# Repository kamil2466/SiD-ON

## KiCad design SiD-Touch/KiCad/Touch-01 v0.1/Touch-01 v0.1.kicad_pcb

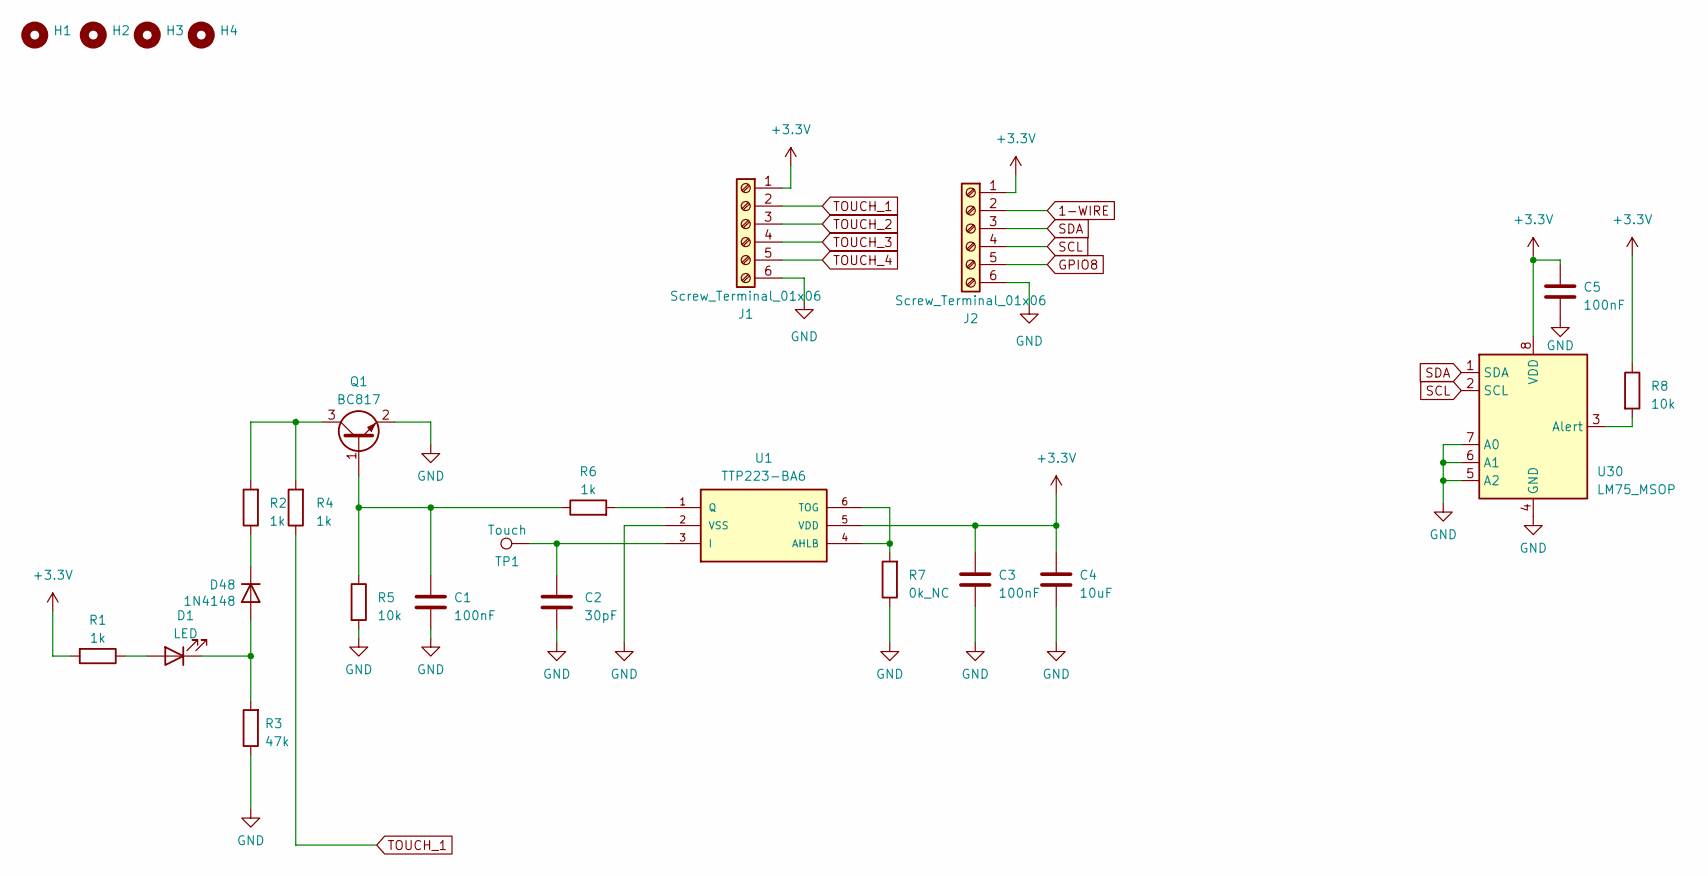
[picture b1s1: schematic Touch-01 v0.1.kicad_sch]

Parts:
C1, C3, C5: 100nF; C_0603_1608Metric
C2: 30pF; C_0603_1608Metric
C4: 10uF; C_0603_1608Metric
D1: LED; LED_1206_3216Metric
D48: 1N4148; D_MiniMELF; JLCPCB C68883
H1, H2, H3, H4: MountingHole; MountingHole_3.2mm_M3_ISO7380_Pad
J1, J2: Screw_Terminal_01x06; PinSocket_1x06_P2.54mm_Vertical
Q1: BC817; SOT-23
R1, R2, R4, R6: 1k; R_0603_1608Metric
R3: 47k; R_0603_1608Metric
R5, R8: 10k; R_0603_1608Metric
R7: 0k_NC; R_0603_1608Metric
TP1: Touch; TestPoint_Pad_D4.0mm
U1: TTP223-BA6; SOT-23-6; MANUFACTURER_PART_NUMBER TTP223-BA6
U30: LM75_MSOP; MSOP-8_3x3mm_P0.65mm

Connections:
1-WIRE: J2.2
+3V3: C3.1, C4.1, C5.1, J1.1, J2.1, R1.2, R8.1, U1.5 (VDD); also elsewhere on the board
GND: C1.2, C2.2, C3.2, C4.2, C5.2, J1.6, J2.6, Q1.2 (E), R3.1, R5.2, R7.1, U1.2 (VSS); also elsewhere on the board
GPIO8: J2.5
unnamed: D1.2 (A), R1.1
unnamed 5: D1.1 (K), R3.2; also elsewhere on the board
unnamed 6: R2.1; also elsewhere on the board
unnamed: C1.1, Q1.1 (B), R5.1, R6.1
unnamed: Q1.3 (C), R2.2, R4.2
unnamed: R7.2, U1.4 (AHLB), U1.6 (TOG)
unnamed: C2.1, TP1.1, U1.3 (I)
unnamed: R6.2, U1.1 (Q)
unnamed 12: R8.2; also elsewhere on the board
SCL: J2.4; also elsewhere on the board
SDA: J2.3; also elsewhere on the board
TOUCH_1: J1.2, R4.1
TOUCH_2: J1.3
TOUCH_3: J1.4
TOUCH_4: J1.5

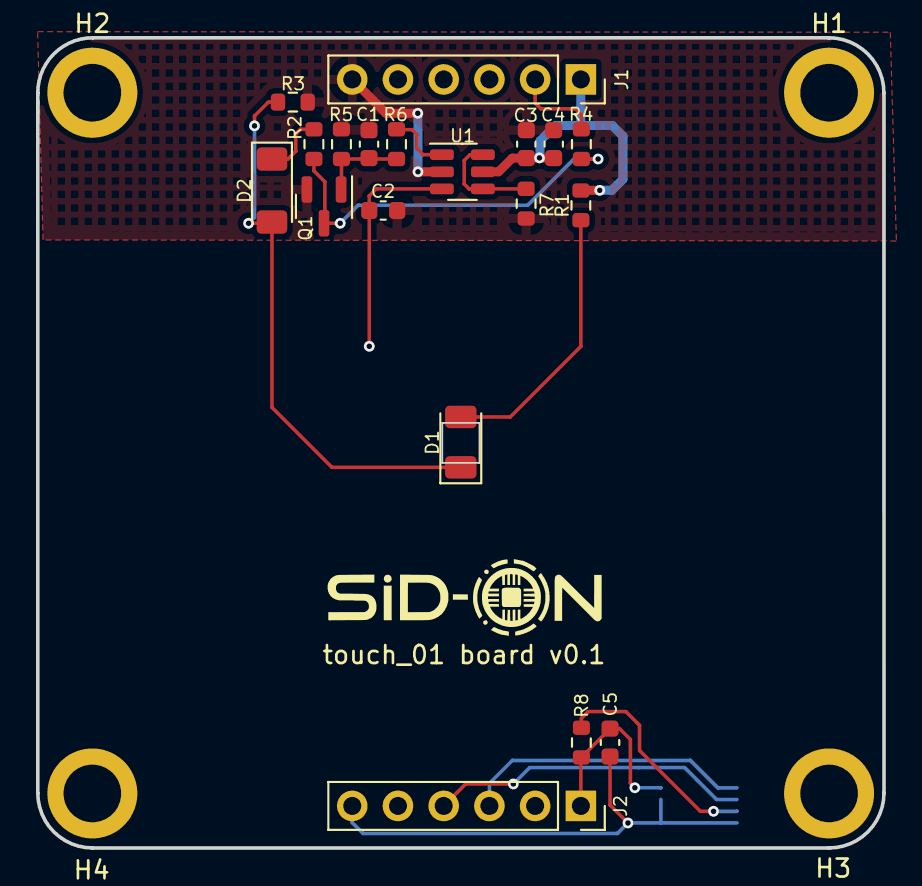
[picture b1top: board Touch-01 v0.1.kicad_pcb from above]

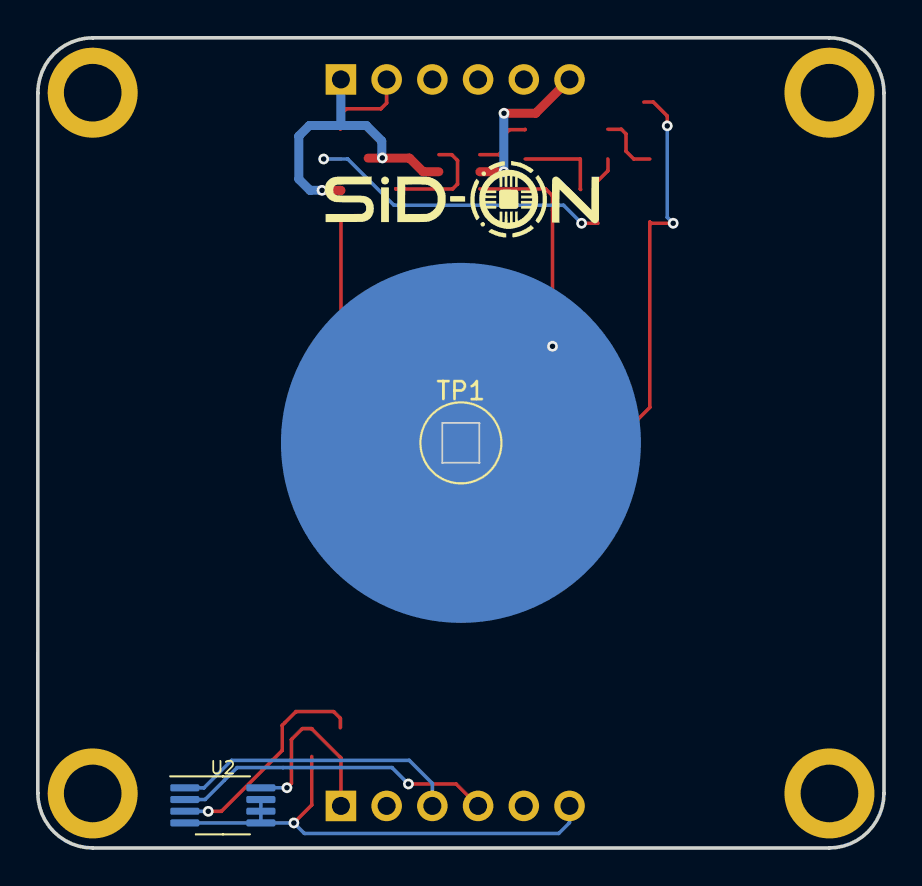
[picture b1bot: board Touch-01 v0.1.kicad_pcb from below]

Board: 2 copper layers, 47.0 x 45.0 mm, 25 parts (2 on the bottom side), 14 nets.

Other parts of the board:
D2: 1N4148; D_MiniMELF
U2: LM75_MSOP; MSOP-8_3x3mm_P0.65mm

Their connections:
+3V3: U2.8 (VDD); also elsewhere on the board
GND: U2.4 (GND), U2.5 (A2), U2.6 (A1), U2.7 (A0); also elsewhere on the board
unnamed 5: D2.2 (A); also elsewhere on the board
unnamed 6: D2.1 (K); also elsewhere on the board
unnamed 12: U2.3 (Alert); also elsewhere on the board
SCL: U2.2 (SCL); also elsewhere on the board
SDA: U2.1 (SDA); also elsewhere on the board

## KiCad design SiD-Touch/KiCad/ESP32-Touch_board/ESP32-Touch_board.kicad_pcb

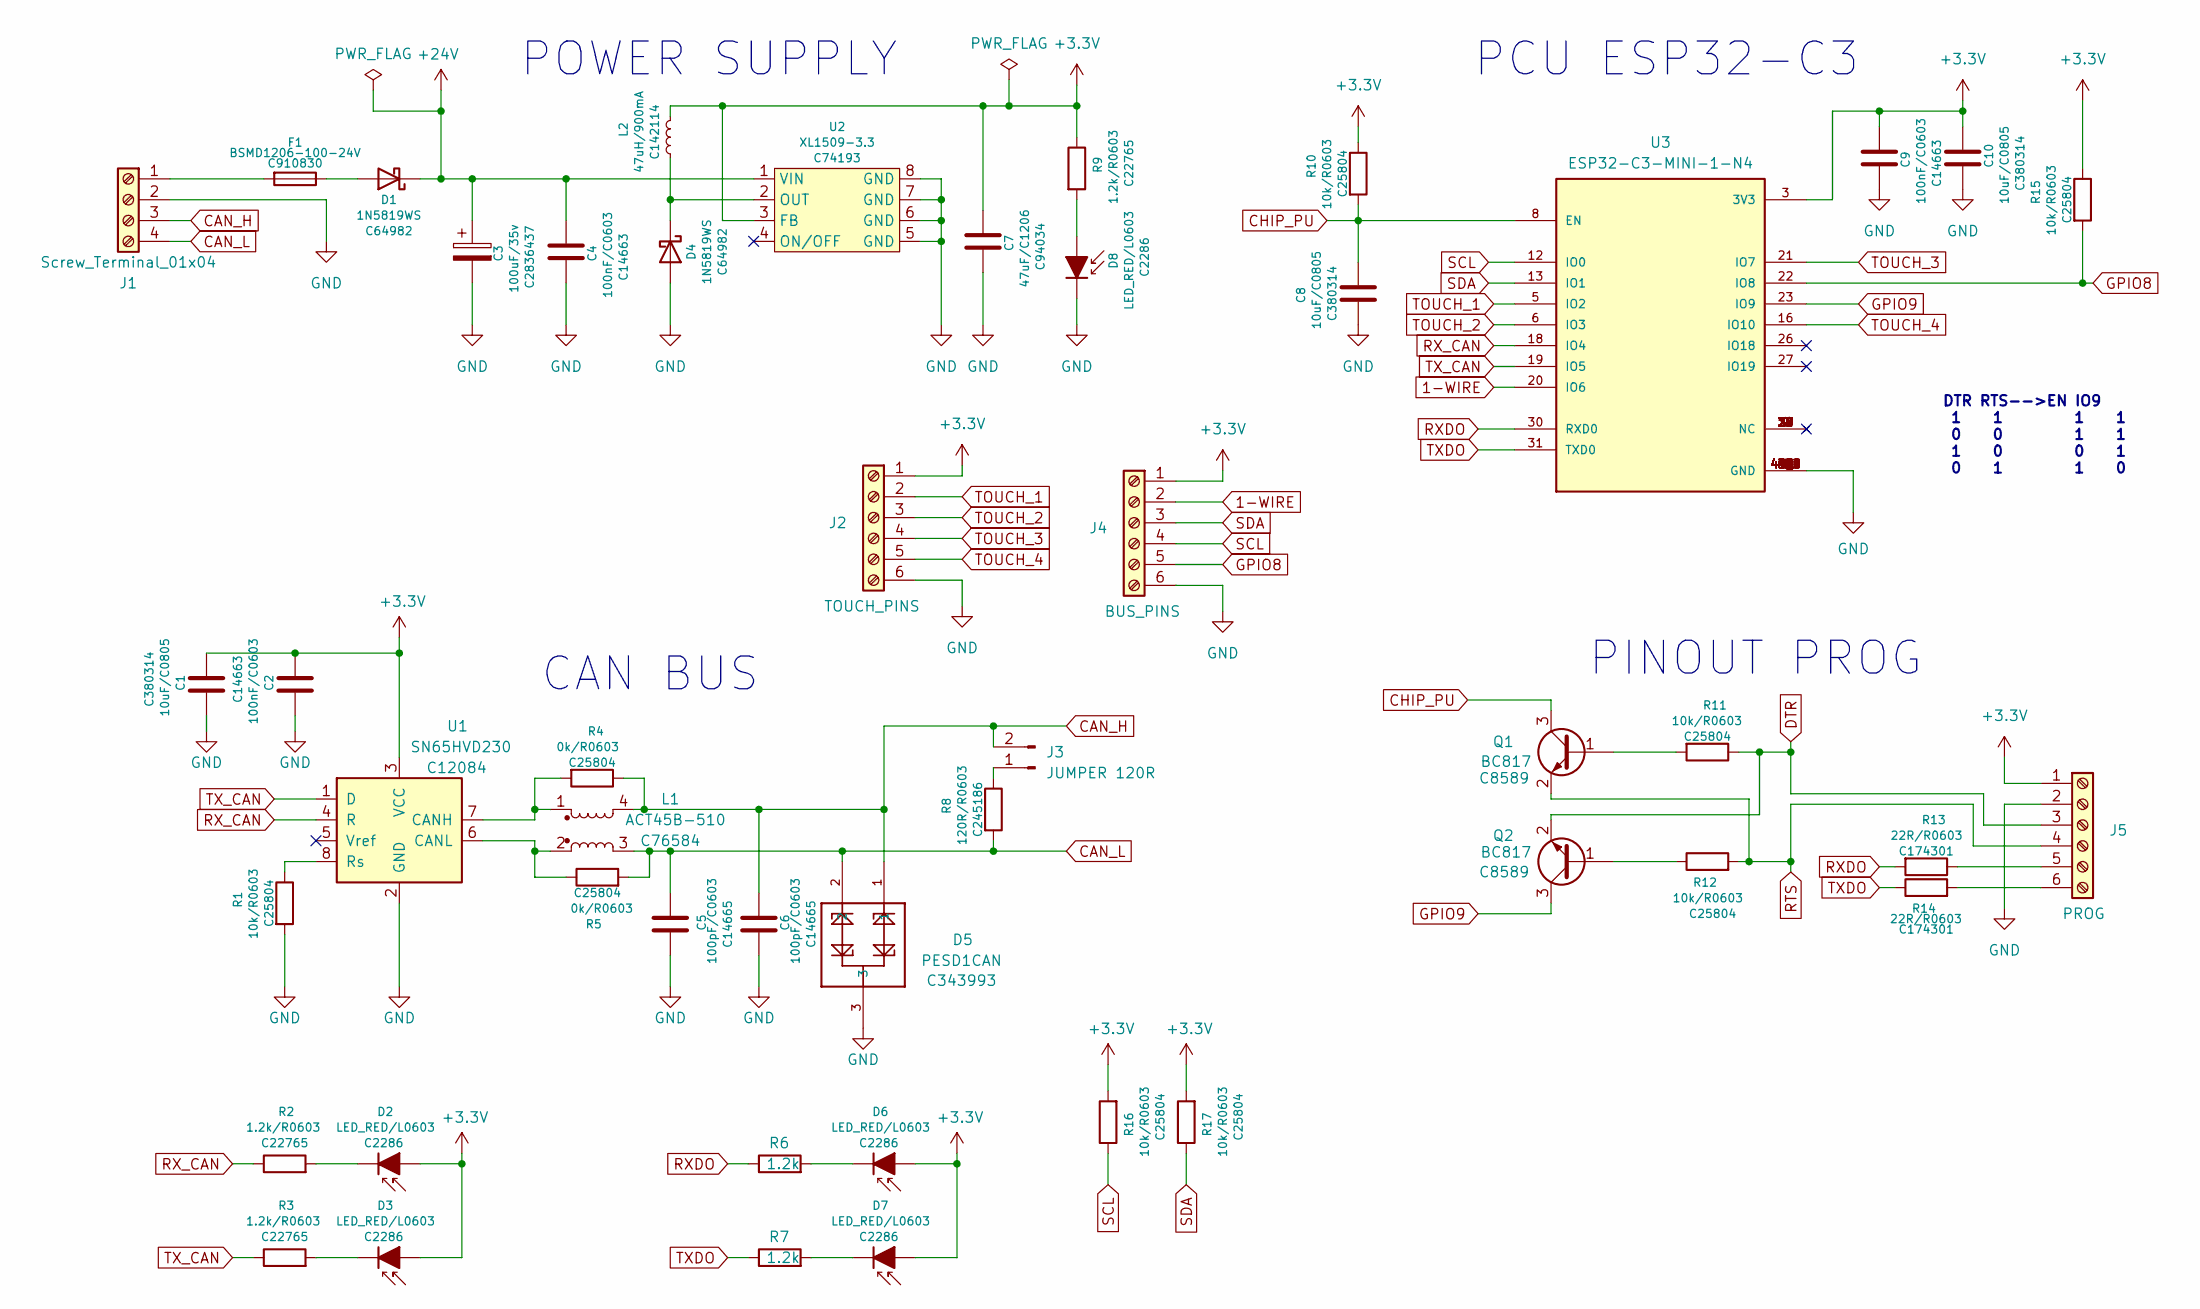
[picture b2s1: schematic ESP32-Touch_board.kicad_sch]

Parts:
C1, C8, C10: 10uF/C0805; C_0603_1608Metric; JLCPCB C380314
C2, C4, C9: 100nF/C0603; C_0603_1608Metric; JLCPCB C14663
C3: 100uF/35v; CP_Elec_6.3x7.7; JLCPCB C2836437
C5, C6: 100pF/C0603; C_0603_1608Metric; JLCPCB C14665
C7: 47uF/C1206; C_1206_3216Metric; JLCPCB C94034
D1, D4: 1N5819WS; D_SOD-323_HandSoldering; JLCPCB C64982
D2, D3, D6, D7, D8: LED_RED/L0603; LED_0603_1608Metric; JLCPCB C2286
D5: PESD1CAN; SOT-23; JLCPCB C343993
F1: BSMD1206-100-24V; Fuse_1206_3216Metric; JLCPCB C910830
J1: Screw_Terminal_01x04; PhoenixContact_MCV_1,5_4-G-3.81_1x04_P3.81mm_Vertical
J2: TOUCH_PINS; PinHeader_1x06_P2.54mm_Vertical
J3: JUMPER 120R; SolderJumper-2_P1.3mm_Open_RoundedPad1.0x1.5mm
J4: BUS_PINS; PinHeader_1x06_P2.54mm_Vertical
J5: PROG; PinHeader_1x06_P2.00mm_Vertical
L1: ACT45B-510; FIL_ACT45B-510-2P-TL003; JLCPCB C76584
L2: 47uH/900mA; L_Sunlord_SWPA5040S; JLCPCB C142114
Q1, Q2: BC817; SOT-23; JLCPCB C8589
R1, R10, R11, R12, R15, R16, R17: 10k/R0603; R_0603_1608Metric; JLCPCB C25804
R2, R3, R9: 1.2k/R0603; R_0603_1608Metric; JLCPCB C22765
R4, R5: 0k/R0603; R_0603_1608Metric; JLCPCB C25804
R6, R7: 1.2k; R_0603_1608Metric; JLCPCB C238881
R8: 120R/R0603; R_0603_1608Metric; JLCPCB C245186
R13, R14: 22R/R0603; R_0603_1608Metric; JLCPCB C174301
U1: SN65HVD230; SOIC-8_3.9x4.9mm_P1.27mm; JLCPCB C12084
U2: XL1509-3.3; SOP-8_3.9x4.9mm_P1.27mm; JLCPPCB C74193
U3: ESP32-C3-MINI-1-N4; XCVR_ESP32-C3-MINI-1-N4; PARTREV v1.0

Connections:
1-WIRE: J4.2, U3.20 (IO6)
+3V3: C1.2, C2.2, C7.1, C9.1, C10.1, D2.2 (A), D3.2 (A), D6.2 (A), D7.2 (A), J2.1, J4.1, J5.1, L2.2, R9.1, R10.1, R15.1, R16.2, R17.2, U1.3 (VCC), U2.3 (FB), U3.3 (3V3)
+24V: C3.1, C4.1, D1.1 (K), U2.1 (VIN)
CAN_H: C6.2, D5.1, J1.3, J3.2, L1.4, R4.1
CAN_L: C5.2, D5.2, J1.4, L1.3, R5.2, R8.2
CHIP_PU: C8.1, Q1.3 (C), R10.2, U3.8 (EN)
DTR: J5.3, Q2.2 (E), R11.1
GND: C1.1, C2.1, C3.2, C4.2, C5.1, C6.1, C7.2, C8.2, C9.2, C10.2, D4.2 (A), D5.3, D8.1 (K), J1.2, J2.6, J4.6, J5.2, R1.2, U1.2 (GND), U2.5 (GND), U2.6 (GND), U2.7 (GND), U2.8 (GND), U3.1 (GND), U3.2 (GND), U3.11 (GND), U3.14 (GND), U3.36 (GND), U3.37 (GND), U3.38 (GND), U3.39 (GND), U3.40 (GND), U3.41 (GND), U3.42 (GND), U3.43 (GND), U3.44 (GND), U3.45 (GND), U3.46 (GND), U3.47 (GND), U3.48 (GND), U3.49_1 (GND), U3.49_2 (GND), U3.49_3 (GND), U3.49_4 (GND), U3.49_5 (GND), U3.49_6 (GND), U3.49_7 (GND), U3.49_8 (GND), U3.49_9 (GND), U3.50 (GND), U3.51 (GND), U3.52 (GND), U3.53 (GND)
GPIO8: J4.5, R15.2, U3.22 (IO8)
GPIO9: Q2.3 (C), U3.23 (IO9)
unnamed: D1.2 (A), F1.1
unnamed: D2.1 (K), R2.2
unnamed: D3.1 (K), R3.2
unnamed: D4.1 (K), L2.1, U2.2 (OUT)
unnamed: D6.1 (K), R6.2
unnamed: D7.1 (K), R7.2
unnamed: D8.2 (A), R9.2
unnamed: F1.2, J1.1
unnamed: J3.1, R8.1
unnamed: J5.5, R13.1
unnamed: J5.6, R14.2
unnamed: Q1.1 (B), R11.2
unnamed: Q2.1 (B), R12.1
unnamed: L1.1, R4.2, U1.7 (CANH)
unnamed: L1.2, R5.1, U1.6 (CANL)
unnamed: R1.1, U1.8 (Rs)
RTS: J5.4, Q1.2 (E), R12.2
RXDO: R6.1, R13.2, U3.30 (RXD0)
RX_CAN: R2.1, U1.4 (R), U3.18 (IO4)
SCL: J4.4, R16.1, U3.12 (IO0)
SDA: J4.3, R17.1, U3.13 (IO1)
TOUCH_1: J2.2, U3.5 (IO2)
TOUCH_2: J2.3, U3.6 (IO3)
TOUCH_3: J2.4, U3.21 (IO7)
TOUCH_4: J2.5, U3.16 (IO10)
TXDO: R7.1, R14.1, U3.31 (TXD0)
TX_CAN: R3.1, U1.1 (D), U3.19 (IO5)

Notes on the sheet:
POWER SUPPLY
PINOUT PROG
CAN BUS
DTR RTS-->EN IO9 1 1 1 1 0 0 1 1 1 0 0 1 0 1 1 0
PCU ESP32-C3

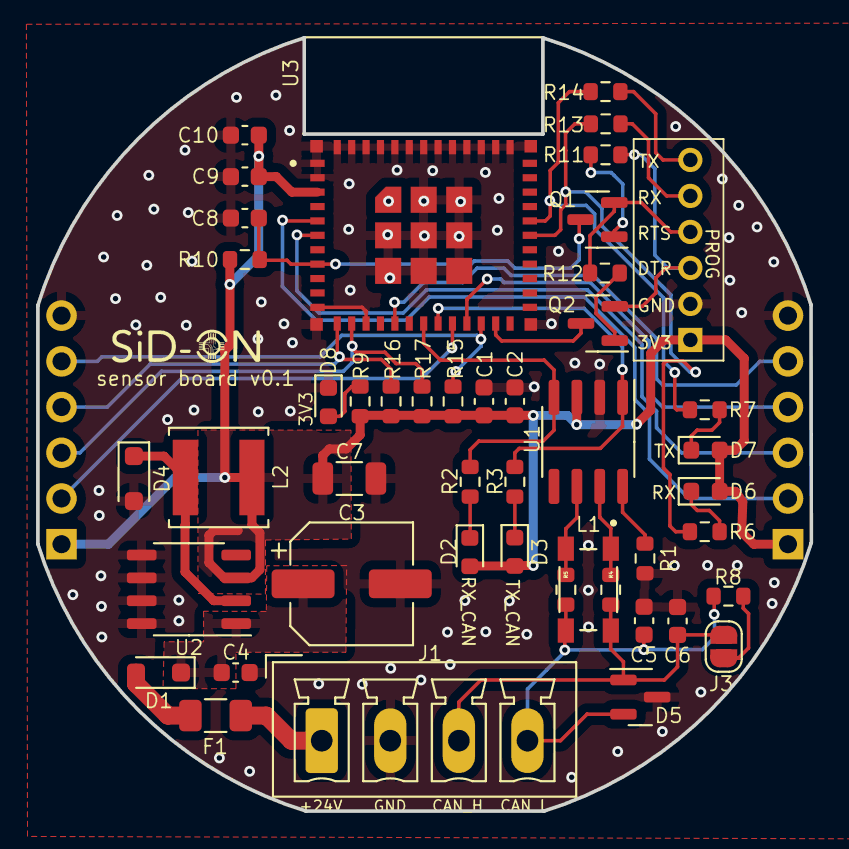
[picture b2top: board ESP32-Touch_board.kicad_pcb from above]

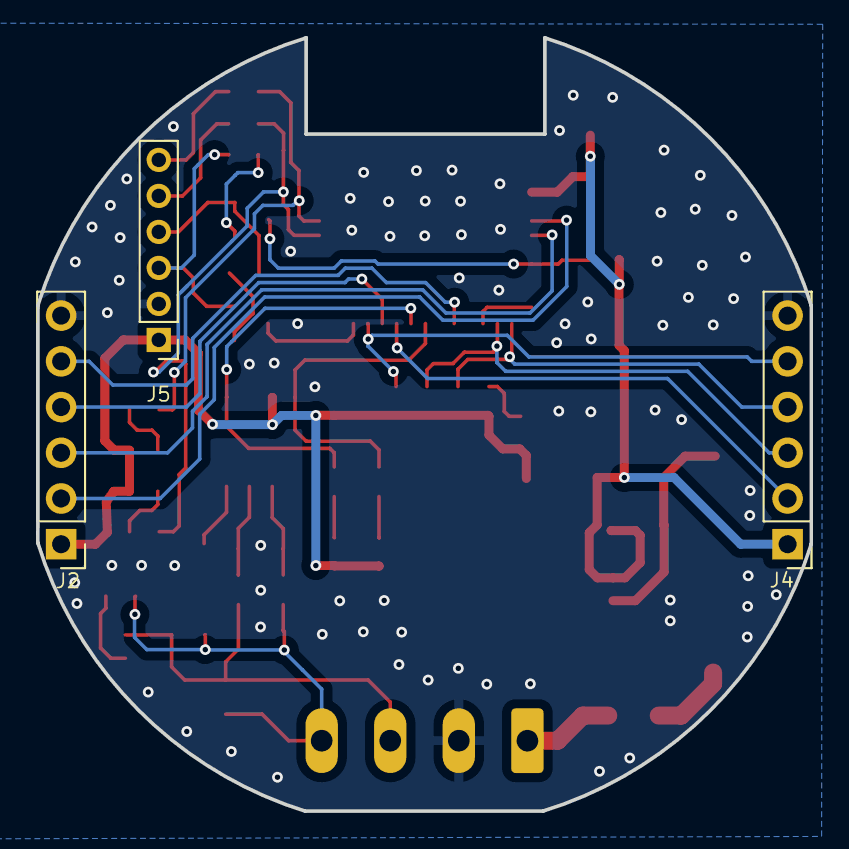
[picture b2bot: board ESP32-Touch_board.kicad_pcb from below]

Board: 2 copper layers, 43.0 x 43.0 mm, 48 parts (3 on the bottom side), 37 nets.

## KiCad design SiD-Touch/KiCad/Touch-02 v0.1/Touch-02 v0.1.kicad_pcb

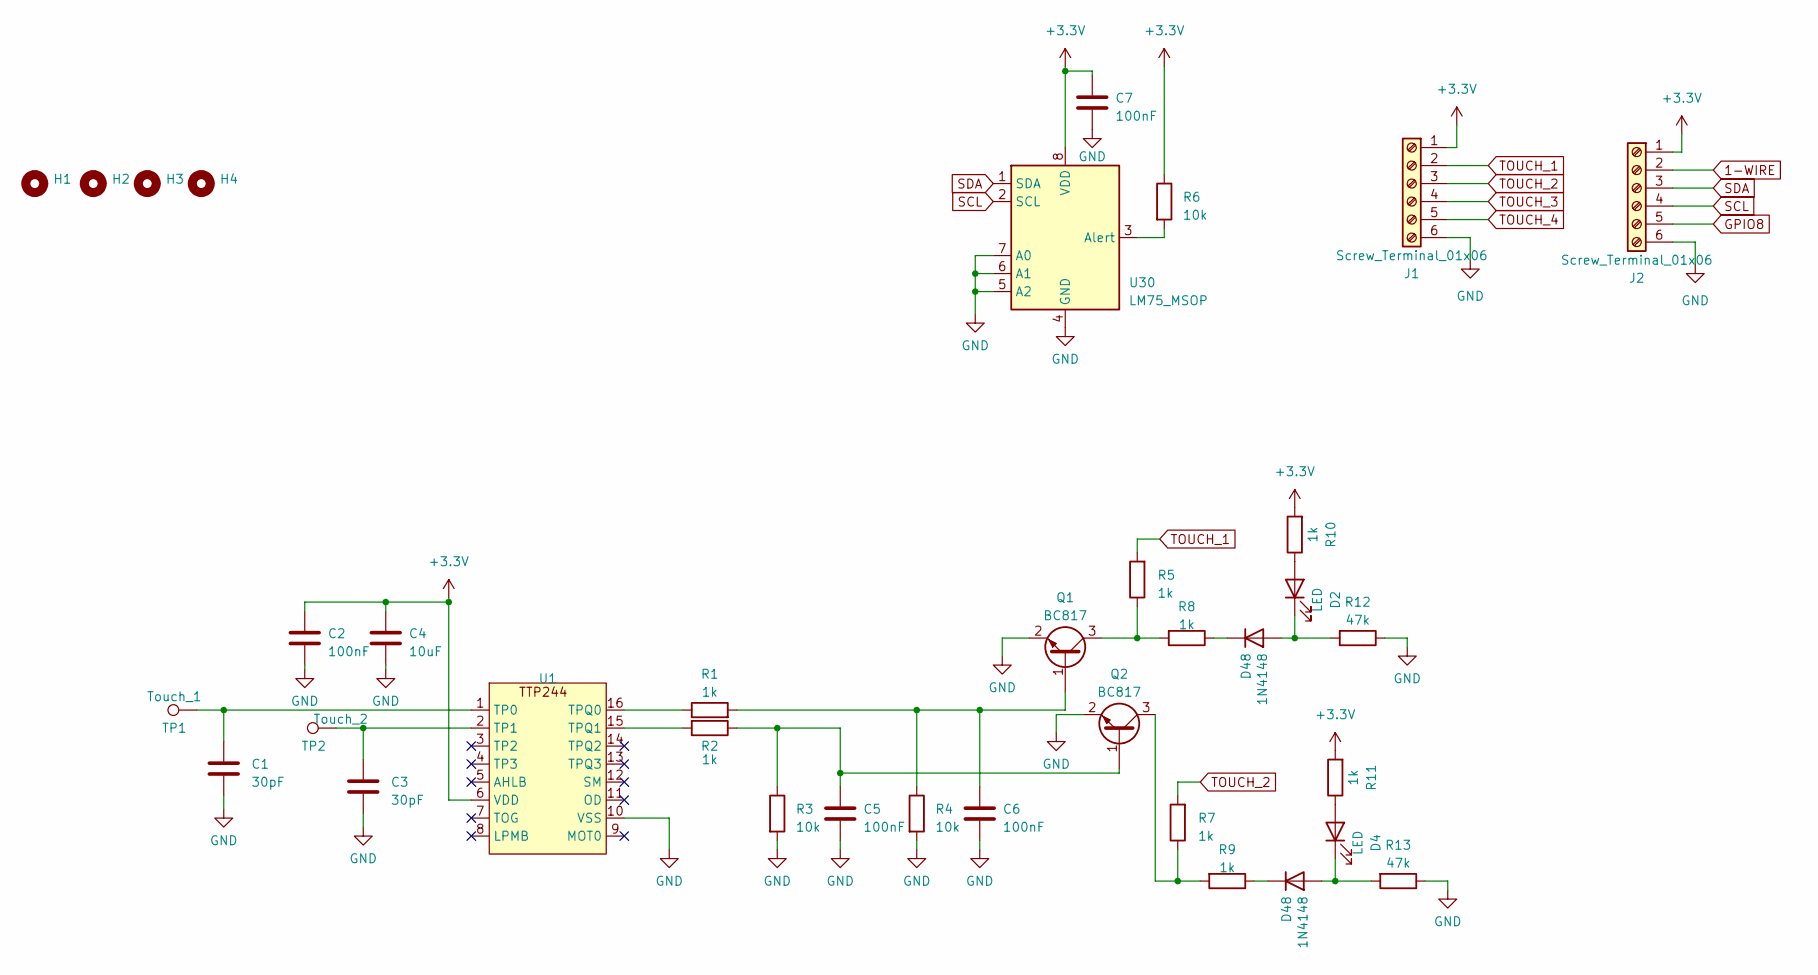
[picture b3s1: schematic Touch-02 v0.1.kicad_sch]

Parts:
C1, C3: 30pF; C_0603_1608Metric
C2, C5, C6, C7: 100nF; C_0603_1608Metric
C4: 10uF; C_0603_1608Metric
D2, D4: LED; LED_1206_3216Metric
D48: 1N4148; D_MiniMELF; JLCPCB C68883
H1, H2, H3, H4: MountingHole; MountingHole_3.2mm_M3_ISO7380_Pad
J1, J2: Screw_Terminal_01x06; PinSocket_1x06_P2.54mm_Vertical
Q1, Q2: BC817; SOT-23
R1, R2, R5, R7, R8, R9, R10, R11: 1k; R_0603_1608Metric
R3, R4, R6: 10k; R_0603_1608Metric
R12, R13: 47k; R_0603_1608Metric
TP1: Touch_1; TestPoint_Pad_D4.0mm
TP2: Touch_2; TestPoint_Pad_D4.0mm
U1: SSOP-16_5.3x6.2mm_P0.65mm
U30: LM75_MSOP; MSOP-8_3x3mm_P0.65mm

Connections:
1-WIRE: J2.2
+3V3: C2.1, C4.1, C7.1, J1.1, J2.1, R6.1, R10.2, R11.2, U1.6 (VDD); also elsewhere on the board
GND: C1.2, C2.2, C3.2, C4.2, C5.2, C6.2, C7.2, J1.6, J2.6, Q1.2 (E), Q2.2 (E), R3.2, R4.2, R12.1, R13.1, U1.10 (VSS); also elsewhere on the board
GPIO8: J2.5
unnamed 4: D2.1 (K), R12.2; also elsewhere on the board
unnamed 5: R8.1; also elsewhere on the board
unnamed: D2.2 (A), R10.1
unnamed 7: D4.1 (K), R13.2; also elsewhere on the board
unnamed 8: R9.1; also elsewhere on the board
unnamed: D4.2 (A), R11.1
unnamed: C6.1, Q1.1 (B), R1.2, R4.1
unnamed: Q1.3 (C), R5.1, R8.2
unnamed: C5.1, Q2.1 (B), R2.1, R3.1
unnamed: Q2.3 (C), R7.1, R9.2
unnamed: C1.1, TP1.1, U1.1 (TP0)
unnamed: C3.1, TP2.1, U1.2 (TP1)
unnamed: R1.1, U1.16 (TPQ0)
unnamed: R2.2, U1.15 (TPQ1)
unnamed 18: R6.2; also elsewhere on the board
SCL: J2.4; also elsewhere on the board
SDA: J2.3; also elsewhere on the board
TOUCH_1: J1.2, R5.2
TOUCH_2: J1.3, R7.2
TOUCH_3: J1.4
TOUCH_4: J1.5

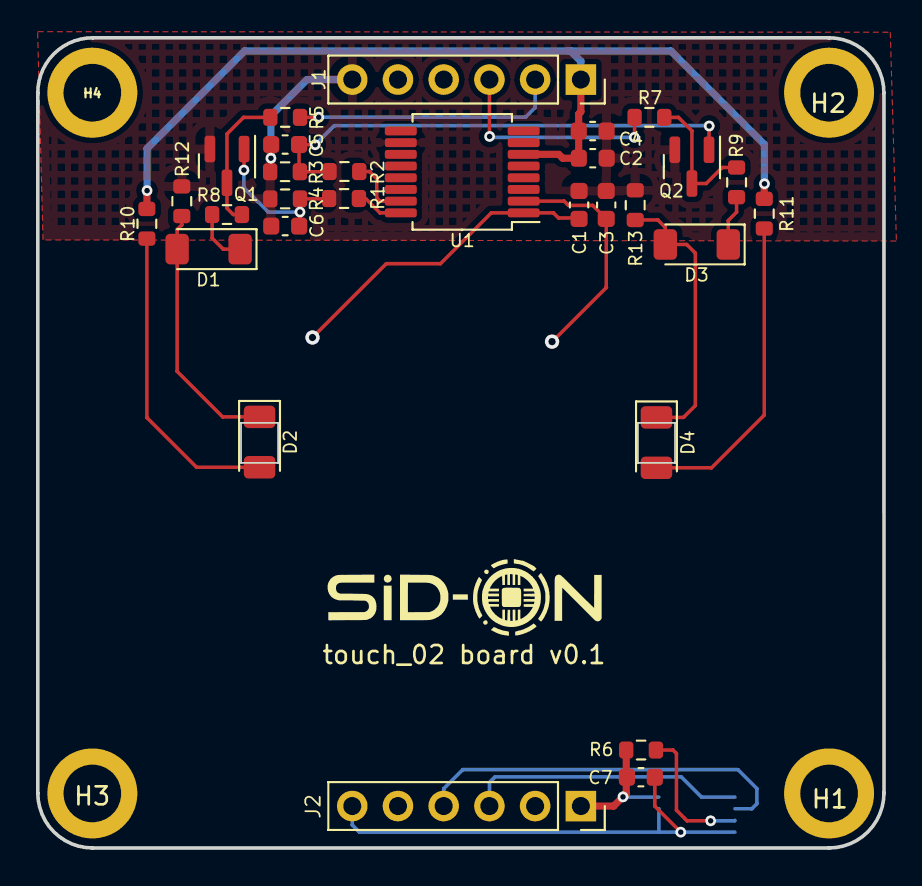
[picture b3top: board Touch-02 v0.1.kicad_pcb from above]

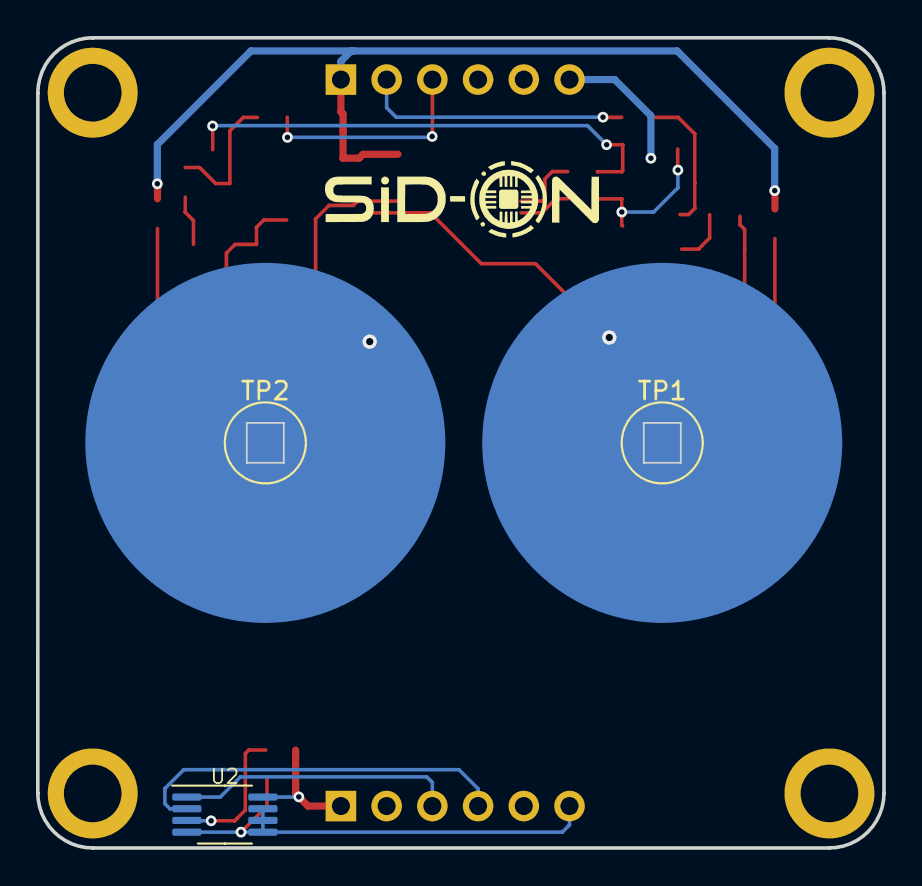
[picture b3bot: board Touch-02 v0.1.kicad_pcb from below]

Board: 2 copper layers, 47.0 x 45.0 mm, 36 parts (3 on the bottom side), 21 nets.

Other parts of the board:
D1, D3: 1N4148; D_MiniMELF
U2: LM75_MSOP; MSOP-8_3x3mm_P0.65mm

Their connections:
+3V3: U2.8 (VDD); also elsewhere on the board
GND: U2.4 (GND), U2.5 (A2), U2.6 (A1), U2.7 (A0); also elsewhere on the board
unnamed 4: D1.2 (A); also elsewhere on the board
unnamed 5: D1.1 (K); also elsewhere on the board
unnamed 7: D3.2 (A); also elsewhere on the board
unnamed 8: D3.1 (K); also elsewhere on the board
unnamed 18: U2.3 (Alert); also elsewhere on the board
SCL: U2.2 (SCL); also elsewhere on the board
SDA: U2.1 (SDA); also elsewhere on the board

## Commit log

2022-11-17 Sid-01
2023-02-27 license
2023-02-27 SiD_01_v0.3.1
2023-03-08 boneio-touch_v0.1
2023-03-08 sid-01_v0.2
2023-03-08 PCB cont
2023-03-21 touch02
2023-03-21 touch02del
